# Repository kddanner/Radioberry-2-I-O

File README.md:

# Radioberry-2-I-O

==================

This is a simple companion board to the Radioberry 2.x to provide I/O and cooling. The minor circuitry used is shamelessly copied from the excellent [Radioberry 2](https://github.com/pa3gsb/Radioberry-2.x) and [Hermes-Lite 2](http://www.hermeslite.com) projects.

I tried to make this board versatile, it can be assembled multiple ways. All SMD parts are on the bottom, but all other components (header/fan/RCA jacks/3.5mm jacks) can be installed on either the top or the bottom. The board pictured has only a 2 pin header installed for the fan, but a 14 pin header can be installed for individual leads or a ribbon cable to be attached to the 5 jacks if they are mounted on a remote panel instead of directly on this board. If installing jacks on the bottom side of this board you'll need to have the SMA connectors on the bottom side of the Radioberry 2 board rather than on top as is usually done. Also, if the fan were installed on the bottom there would not be a lot of clearance between the fan and the Radioberry 2 board so you'll need low profile heatsinks and/or longer headers connecting the 2 boards to get the needed clearance. There is enough room for the I/O header to be a 90-degree header to keep the profile lower if wanted.

The zero-ohm resistors, numbered R10x are only needed when the jacks are installed on this board, and they only need to be installed in either the boxes silkscreened TOP or BTM, never both.

This cheap "case" is some of the parts from one that is meant for a pi cluster stack, available here: [Amazon link](https://www.amazon.com/gp/product/B07JP2TFJY/ref=ppx_yo_dt_b_search_asin_title?ie=UTF8&psc=1)

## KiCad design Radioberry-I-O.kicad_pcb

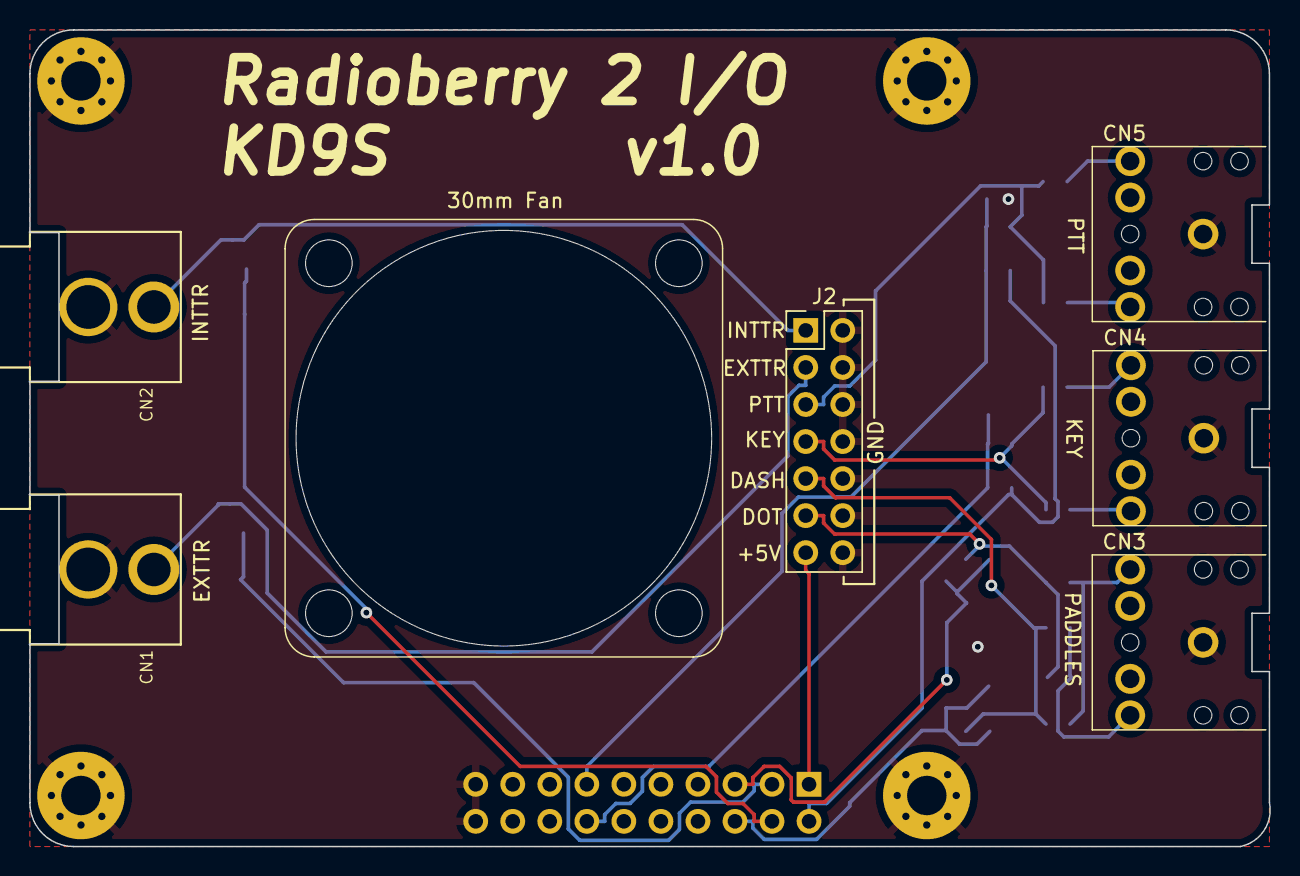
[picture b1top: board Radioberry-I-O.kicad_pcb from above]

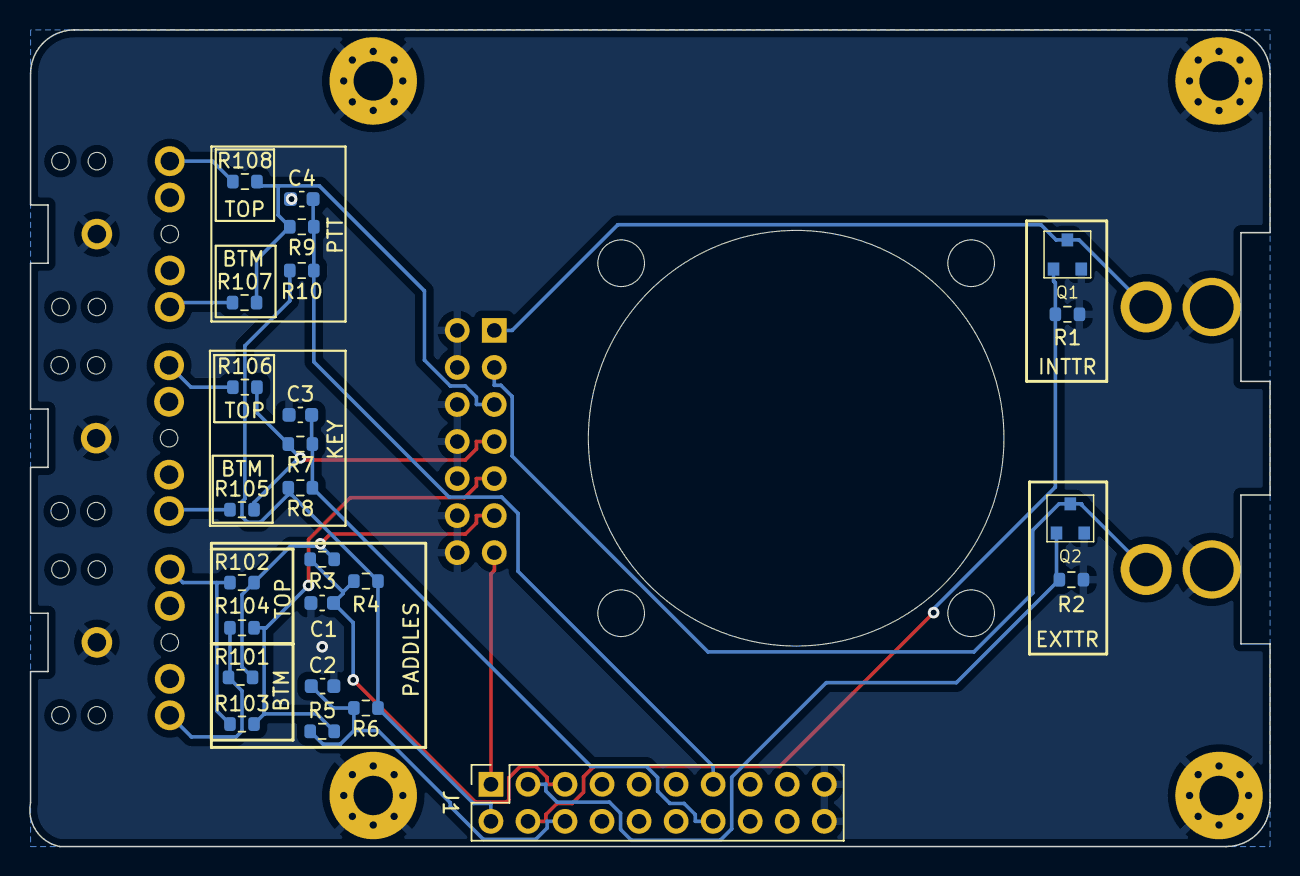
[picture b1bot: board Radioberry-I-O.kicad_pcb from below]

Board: 2 copper layers, 85.0 x 56.0 mm, 36 parts (25 on the bottom side), 21 nets.

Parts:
C1, C2, C3, C4: 1uf; C_0603_1608Metric
CN1, CN2: RCA Jack; PhonoRcaRCJ-04x
CN3, CN4, CN5: 3.5mm stereo jack; STEREO
J1: 2x10 female header 2.54mm; PinSocket_2x10_P2.54mm_Vertical
J2: 2x7 male header 2.54mm; PinHeader_2x07_P2.54mm_Vertical
M1: 30mm Fan; fan30_big_hole
Q1, Q2: NUD3160LT1G; SOT23_3
R1, R2: 4.7K; R_0603_1608Metric
R3, R5, R7, R9: 100; R_0603_1608Metric
R4, R6, R8, R10: 2.2k; R_0603_1608Metric
R101, R102, R103, R104, R105, R106, R107, R108: 0; R_0603_1608Metric
REF1, REF2, REF3, REF4: MountingHole_2.7mm_Pad_Via

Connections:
+3V3: J1.2, R4.2, R6.1, R8.2, R10.2
+5V: J1.1, J2.13
DASH: J2.9, R5.2, R103.2, R104.2
DOT: J2.11, R3.2, R101.2, R102.2
EXTTR: CN1.1, J2.3, Q2.3 (D)
GND: C1.1, C2.2, C3.1, C4.1, CN1.2, CN2.2, CN3.1, CN4.1, CN5.1, J1.19, J1.20, J2.2, J2.4, J2.6, J2.8, J2.10, J2.12, J2.14, Q1.2 (S), Q2.2 (S), R1.2, R2.2, REF1.1, REF2.1, REF3.1, REF4.1
INTTR: CN2.1, J2.1, Q1.3 (D)
KEY: J2.7, R7.2, R105.2, R106.2
unnamed: CN3.2, R102.1, R103.1
unnamed: CN3.3, R101.1, R104.1
unnamed: CN4.2, R106.1
unnamed: CN4.3, R105.1
unnamed: CN5.2, R108.1
unnamed: CN5.3, R107.1
PTT: J2.5, R9.2, R107.2, R108.2
rb_dash: C2.1, J1.6, R5.1, R6.2
rb_dot: C1.2, J1.5, R3.1, R4.1
rb_exttr: J1.3, Q2.1 (G), R2.1
rb_inttr: J1.4, Q1.1 (G), R1.1
rb_key: C3.2, J1.14, R7.1, R8.1
rb_ptt: C4.2, J1.13, R9.1, R10.1

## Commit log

2022-01-28 Attempting to add images
2022-01-28 BOM cleanup
2022-02-14 Update BOM & readme
2022-02-14 typos in readme
